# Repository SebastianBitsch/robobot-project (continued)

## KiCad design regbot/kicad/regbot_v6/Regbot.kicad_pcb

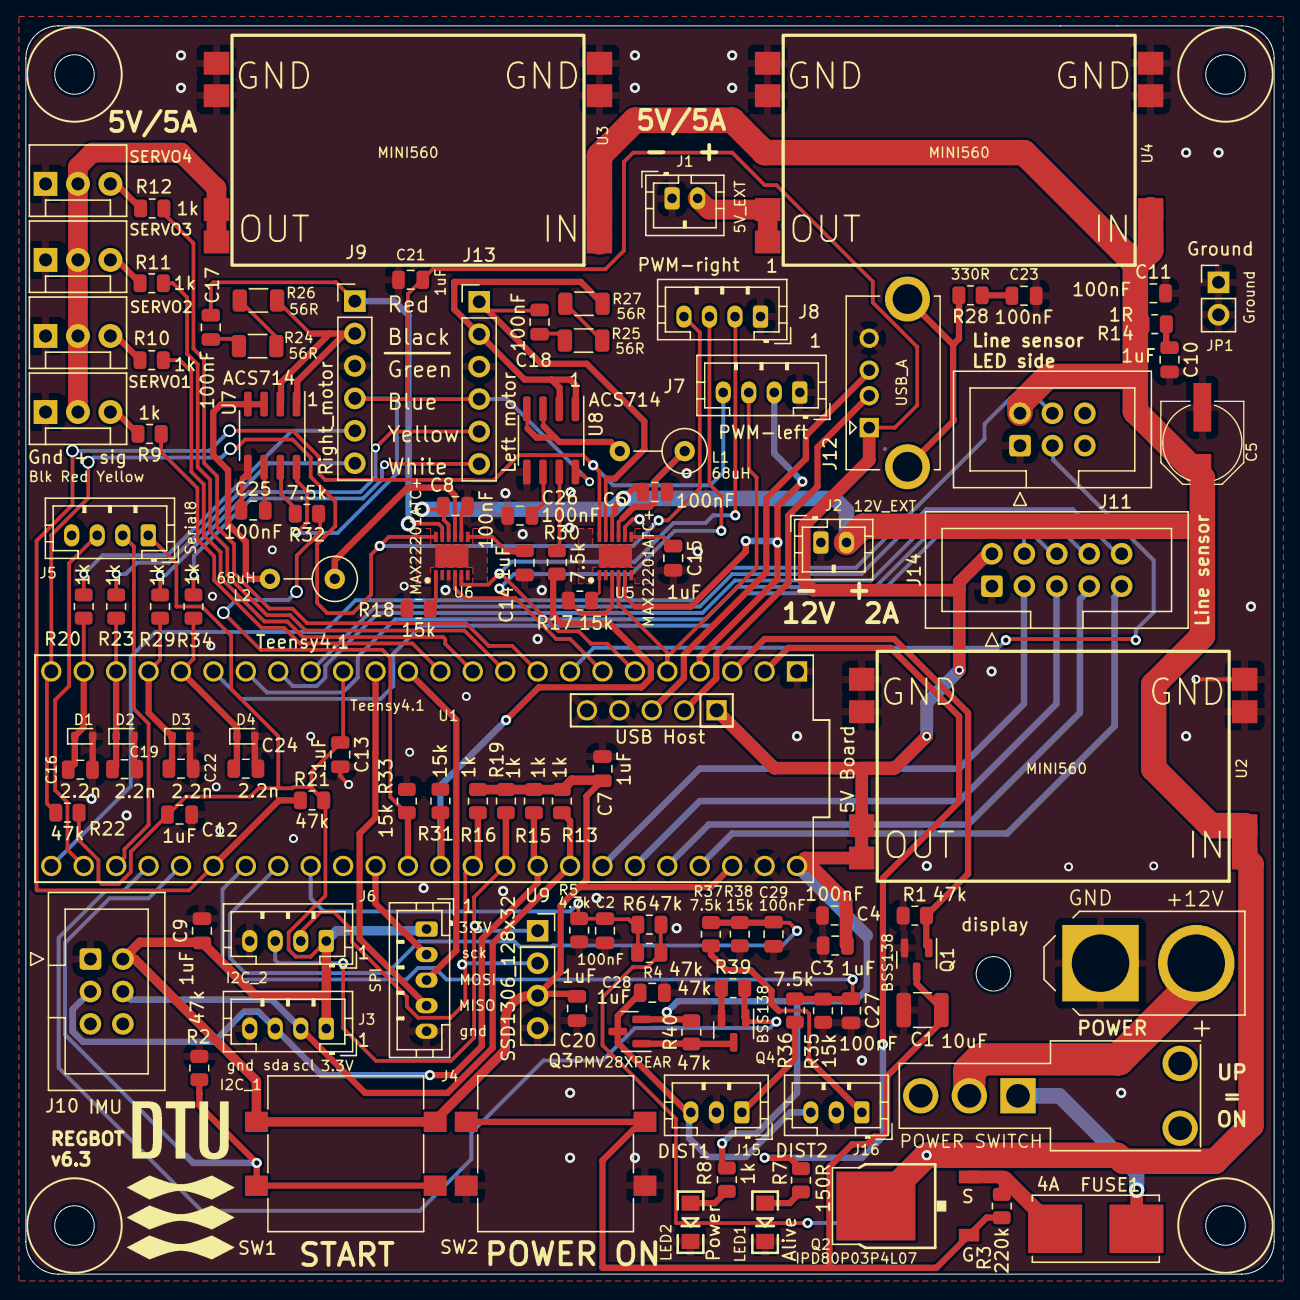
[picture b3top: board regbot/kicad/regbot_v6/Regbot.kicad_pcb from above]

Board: 2 copper layers, 97.8 x 97.8 mm, 123 parts (1 on the bottom side), 91 nets.

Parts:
@HOLE0, @HOLE1, @HOLE2, @HOLE3: (no value)
C1: 10uF; C_1210_3225Metric
C2, C4, C6, C8, C11, C17, C18, C23, C25, C26, C27, C29: 100nF; C_0805_2012Metric
C3, C7, C9, C10, C12, C13, C14, C15, C20, C21, C28: 1uF; C_0805_2012Metric
C5: 47uF; PANASONIC_D_XL
C16, C19, C22, C24: 2.2n; C_0805_2012Metric
D1, D2, D3, D4: DZ2S033X0L; D_SOD-523
FUSE1: 4A; Fuseholder_Littelfuse_Nano2_154x
J1: 5V_EXT; JST_PH_B2B-PH-K_1x02_P2.00mm_Vertical
J2: 12V_EXT; JST_PH_B2B-PH-K_1x02_P2.00mm_Vertical
J3: I2C_1; JST_PH_B4B-PH-K_1x04_P2.00mm_Vertical
J4: SPI; JST_PH_B5B-PH-K_1x05_P2.00mm_Vertical
J5: Serial8; JST_PH_B4B-PH-K_1x04_P2.00mm_Vertical
J6: I2C_2; JST_PH_B4B-PH-K_1x04_P2.00mm_Vertical
J7: PWM_L; JST_PH_B4B-PH-K_1x04_P2.00mm_Vertical
J8: PWM_R; JST_PH_B4B-PH-K_1x04_P2.00mm_Vertical
J9: Right_motor; PinHeader_1x06_P2.54mm_Vertical
J10, J11: IDC-Header_2x03_P2.54mm_Vertical
J12: USB_A; USB_A_ASSMANN_A-TOP_VERTICAL
J13: Left motor; PinHeader_1x06_P2.54mm_Vertical
J14: IDC-Header_2x05_P2.54mm_Vertical
J15, J16: Conn_01x03; JST_PH_B3B-PH-K_1x03_P2.00mm_Vertical
JP1: Ground; PinHeader_1x02_P2.54mm_Vertical
L1, L2: 68uH; L_Axial_L7.0mm_D3.3mm_P5.08mm_Vertical_Fastron_MICC
LED1: LTST-C150KRKT; LED-1206
LED2: LTST-C150TRKT; LED-1206
POWER1: XT60
Q1, Q4: BSS138; SOT-23
Q2: IRF?5305R; D-PAK_TO252AA
Q3: PMV28XPEAR; SOT-23
R1, R2, R4, R6, R21, R22, R39, R40: 47k; R_0805_2012Metric
R3: 220k; R_0805_2012Metric
R5: 4.7k; R_0805_2012Metric
R7: 150R; R_0805_2012Metric
R8, R9, R10, R11, R12, R13, R15, R16, R19, R20, R23, R29, R34: 1k; R_0805_2012Metric
R14: 1R; R_0805_2012Metric
R17, R18, R31, R33, R35, R38: 15k; R_0805_2012Metric
R24, R25, R26, R27: 56R; R_1206_3216Metric
R28: 330R; R_0805_2012Metric
R30, R32, R36, R37: 7.5k; R_0805_2012Metric
SERVO1, SERVO2, SERVO3, SERVO4: M03POLAR; MOLEX-1X3
SW1, SW2: PHAP5-50VA2Q2S2N; SW_APEM_12x12
SWITCH1: RS-PRO-SPDT-1MS1T2B3M7QES; RS-PRO-1MS1T2B3M7QES
U1: Teensy4.1; Teensy41
U2, U3, U4: MINI560
U5, U6: MAX22201ATC+; SON50P300X300X80-13N
U7, U8: ACS714ELCTR-05B; SOIC-8_3.9x4.9mm_P1.27mm
U9: SSD1306_128x32; PinSocket_1x04_P2.54mm_Vertical
U$1, U$1#2: DTUMEDIUM-9MM; DTU-MEDIUM-9MM
display: MountingHole_2.7mm_M2.5

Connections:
3.3V: C7.1, C9.1, C12.1, C13.1, C20.1, J3.1, J4.1, J5.1, J6.1, J10.2, R13.2, R15.2, R16.2, R19.2, R21.2, R22.2, SW1.2, U1.15 (3V3), U1.46 (3V3), U9.3 (VCC)
5V: C3.1, C4.1, C21.1, J9.4, J12.1 (VBUS), J13.4, J14.2, Q3.2 (S), R8.2, R40.2, U1.48 (VIN), U1.55 (5V), U2.3 (OUT), U7.8 (VCC), U8.8 (VCC)
12V: C5.+, C6.1, C8.1, C11.1, J2.2, J11.2, Q2.4 (D), R4.2, R6.2, R14.2, U2.1 (IN), U3.1 (IN), U4.1 (IN), U5.10 (V_M), U6.10 (V_M)
/5V_EXT: J1.2, U4.3 (OUT)
/5V_SERVO: SERVO1.2, SERVO2.2, SERVO3.2, SERVO4.2, U3.3 (OUT)
/12V_RAW: POWER1.P$2 (2), SWITCH1.P$2 (P2)
/D+: J12.3 (D+), U1.57 (D+)
/D-: J12.2 (D-), U1.56 (D-)
/DIST1: C27.1, R35.2, R36.1, U1.31 (39_MISO1_OUT1A)
/DIST2: C29.1, R37.1, R38.2, U1.32 (40_A16)
/LEFT-~FAULT: J7.4, R21.1, U1.30 (38_CS1_IN1), U5.12 (~FAULT)
/LEFT_ENC_A: C22.1, D3.1 (K), R29.1, U1.21 (29_TX7)
/LEFT_ENC_B: C24.1, D4.1 (K), R34.1, U1.20 (28_RX7)
/LEFT_IN_+: J7.3, U1.5 (3_LRCLK2), U5.4 (IN1)
/LEFT_IN_-: J7.2, U1.4 (2_OUT2), U5.5 (IN2)
/LEFT_MOTOR_+: C18.1, J13.1, U5.11 (OUT1)
/LEFT_MOTOR_-: J13.2, R27.2, U8.1 (IP+), U8.2 (IP+)
/LEFT_MOT_CURRENT: R30.1, R31.2, U1.37 (15_A1_RX3_SPDIF_IN)
/LINE_LED_HIGH: J11.3, U1.8 (6_OUT1D)
/LINE_LED_LOW: J11.4, U1.25 (33_MCLK2)
/LS0: J14.3, U1.42 (20_A6_TX5_LRCLK1)
/LS1: J14.4, U1.19 (27_A13_SCK1)
/LS2: J14.9, U1.45 (23_A9_CRX1_MCLK1)
/LS3: J14.5, U1.43 (21_A7_RX5_BCLK1)
/LS4: J14.6, U1.18 (26_A12_MOSI1)
/LS5: J14.10, U1.16 (24_A10_TX6_SCL2)
/LS6: J14.7, U1.44 (22_A8_CTX1)
/LS7: J14.8, U1.17 (25_A11_RX6_SDA2)
/MISO: J4.4, U1.14 (12_MISO_MQSL)
/MOSI: J4.3, U1.13 (11_MOSI_CTX1)
/PWM1: R9.1, U1.12 (10_CS_MQSR)
/PWM2: R10.1, U1.11 (9_OUT1C)
/PWM3: R11.1, U1.10 (8_TX2_IN1)
/PWM4: R12.1, U1.9 (7_RX2_OUT1A)
/PWR_IR: Q4.1 (G), R39.2, U1.28 (36_CS)
/PWR_ROBOT: Q1.1 (G), R1.2, U1.3 (1_TX1_CTX2_MISO1)
/RIGHT-~FAULT: J8.4, R22.1, U1.24 (32_OUT1B), U6.12 (~FAULT)
/RIGHT_ENC_A: C16.1, D1.1 (K), R20.1, U1.23 (31_CTX3)
/RIGHT_ENC_B: C19.1, D2.1 (K), R23.1, U1.22 (30_CRX3)
/RIGHT_IN_+: J8.3, U1.7 (5_IN2), U6.4 (IN1)
/RIGHT_IN_-: J8.2, U1.6 (4_BCLK2), U6.5 (IN2)
/RIGHT_MOTOR_+: C17.1, J9.1, U6.11 (OUT1)
/RIGHT_MOTOR_-: J9.2, R26.2, U7.1 (IP+), U7.2 (IP+)
/RIGHT_MOT_CURRENT: R32.1, R33.2, U1.36 (14_A0_TX3_SPDIF_OUT)
/RX8: J5.3, U1.26 (34_RX8)
/SCK&BUILTIN_LED: J4.2, U1.35 (13_SCK_LED)
/SCL: J3.2, J10.4, R13.1, U1.41 (19_A5_SCL)
/SCL1: J6.2, R16.1, U1.38 (16_A2_RX4_SCL1), U9.2 (SCL)
/SDA: J3.3, J10.3, R15.1, U1.40 (18_A4_SDA)
/SDA1: J6.3, R19.1, U1.39 (17_A3_TX4_SDA1), U9.1 (SDA)
/START: R2.2, SW1.1, U1.29 (37_CS)
/STATUS_LED: R7.2, U1.2 (0_RX1_CRX2_CS1)
/TX8: J5.2, U1.27 (35_TX8)
/V_BAT: C2.1, R4.1, R5.2, R6.1, U1.33 (41_A17)
GND: C1.2, C2.2, C3.2, C4.2, C5.-, C6.2, C7.2, C8.2, C9.2, C10.2, C11.2, C12.2, C13.2, C14.2, C15.2, C16.2, C19.2, C20.2, C21.2, C22.2, C23.2, C24.2, C25.1, C26.1, C27.2, C28.2, C29.2, D1.2 (A), D2.2 (A), D3.2 (A), D4.2 (A), J1.1, J2.1, J3.4, J4.5, J5.4, J6.4, J7.1, J8.1, J9.3, J10.1, J11.1, J12.4 (GND), J13.3, J14.1, J15.2, J16.2, JP1.1 (A), JP1.2 (B), LED1.C, LED2.C, POWER1.P$1 (1), Q1.2 (S), Q4.2 (S), R1.1, R2.1, R5.1, R17.1, R18.1, R31.1, R33.1, R35.1, R38.1, R39.1, SERVO1.1, SERVO2.1, SERVO3.1, SERVO4.1, SW2.1, U1.1 (GND), U1.34 (GND), U1.47 (GND), U1.58 (GND), U1.59 (GND), U2.2 (GND), U2.4 (GND), U3.2 (GND), U3.4 (GND), U4.2 (GND), U4.4 (GND), U5.3 (GNDP), U5.8 (GNDA), U6.3 (GNDP), U6.8 (GNDA), U7.5 (GND), U8.5 (GND), U9.4 (GND)
unnamed: C10.1, R14.1
unnamed: C17.2, R24.1
unnamed: C18.2, R25.1
unnamed: C23.1, R28.1
unnamed: FUSE1.1 (PIN1), Q2.3 (S), R3.2
unnamed: FUSE1.2 (PIN2), SWITCH1.P$1 (O1)
unnamed: J9.5, R20.2
unnamed: J9.6, R23.2
unnamed: J12.5 (Shield), R28.2
unnamed: J13.5, R29.2
unnamed: J13.6, R34.2
unnamed: J15.1, R36.2
unnamed: C28.1, J15.3, J16.3, Q3.3 (D)
unnamed: J16.1, R37.2
unnamed: L1.2, U8.3 (IP-), U8.4 (IP-)
unnamed: L2.2, U7.3 (IP-), U7.4 (IP-)
unnamed: LED1.A, R7.1
unnamed: LED2.A, R8.1
unnamed: C1.1, Q1.3 (D), Q2.1 (G), R3.1, SW2.2
unnamed: Q3.1 (G), Q4.3 (D), R40.1
unnamed: R9.2, SERVO1.3
unnamed: R10.2, SERVO2.3
unnamed: R11.2, SERVO3.3
unnamed: R12.2, SERVO4.3
unnamed: R24.2, R26.1
unnamed: R25.2, R27.1
unnamed: R17.2, U5.1 (ILIM)
unnamed: L1.1, U5.9 (OUT2)
unnamed: C15.1, U5.7 (V_18)
unnamed: R18.2, U6.1 (ILIM)
unnamed: L2.1, U6.9 (OUT2)
unnamed: C14.1, U6.7 (V_18)
unnamed: C25.2, U7.6 (FILTER)
unnamed: R32.2, U7.7 (VIOUT)
unnamed: C26.2, U8.6 (FILTER)
unnamed: R30.2, U8.7 (VIOUT)

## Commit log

2024-02-02 entire robot code base
2024-02-14 testing
2024-02-14 added some comment of what to do
2024-02-16 added regbot
2024-02-16 more files
2024-02-16 removed logs etc.
2024-02-23 main vel test
2024-02-23 ignore ds
2024-02-23 template plan for golf
2024-02-23 include robot.ini
2024-02-23 changed 100 to 200 a lot of places
2024-02-23 comments
2024-02-23 added robot.ini
2024-02-23 stuff
2024-03-08 some control stuff
2024-03-08 goto
2024-03-08 some work
2024-03-14 linemode
2024-03-15 line offset
2024-03-15 disable line mode
